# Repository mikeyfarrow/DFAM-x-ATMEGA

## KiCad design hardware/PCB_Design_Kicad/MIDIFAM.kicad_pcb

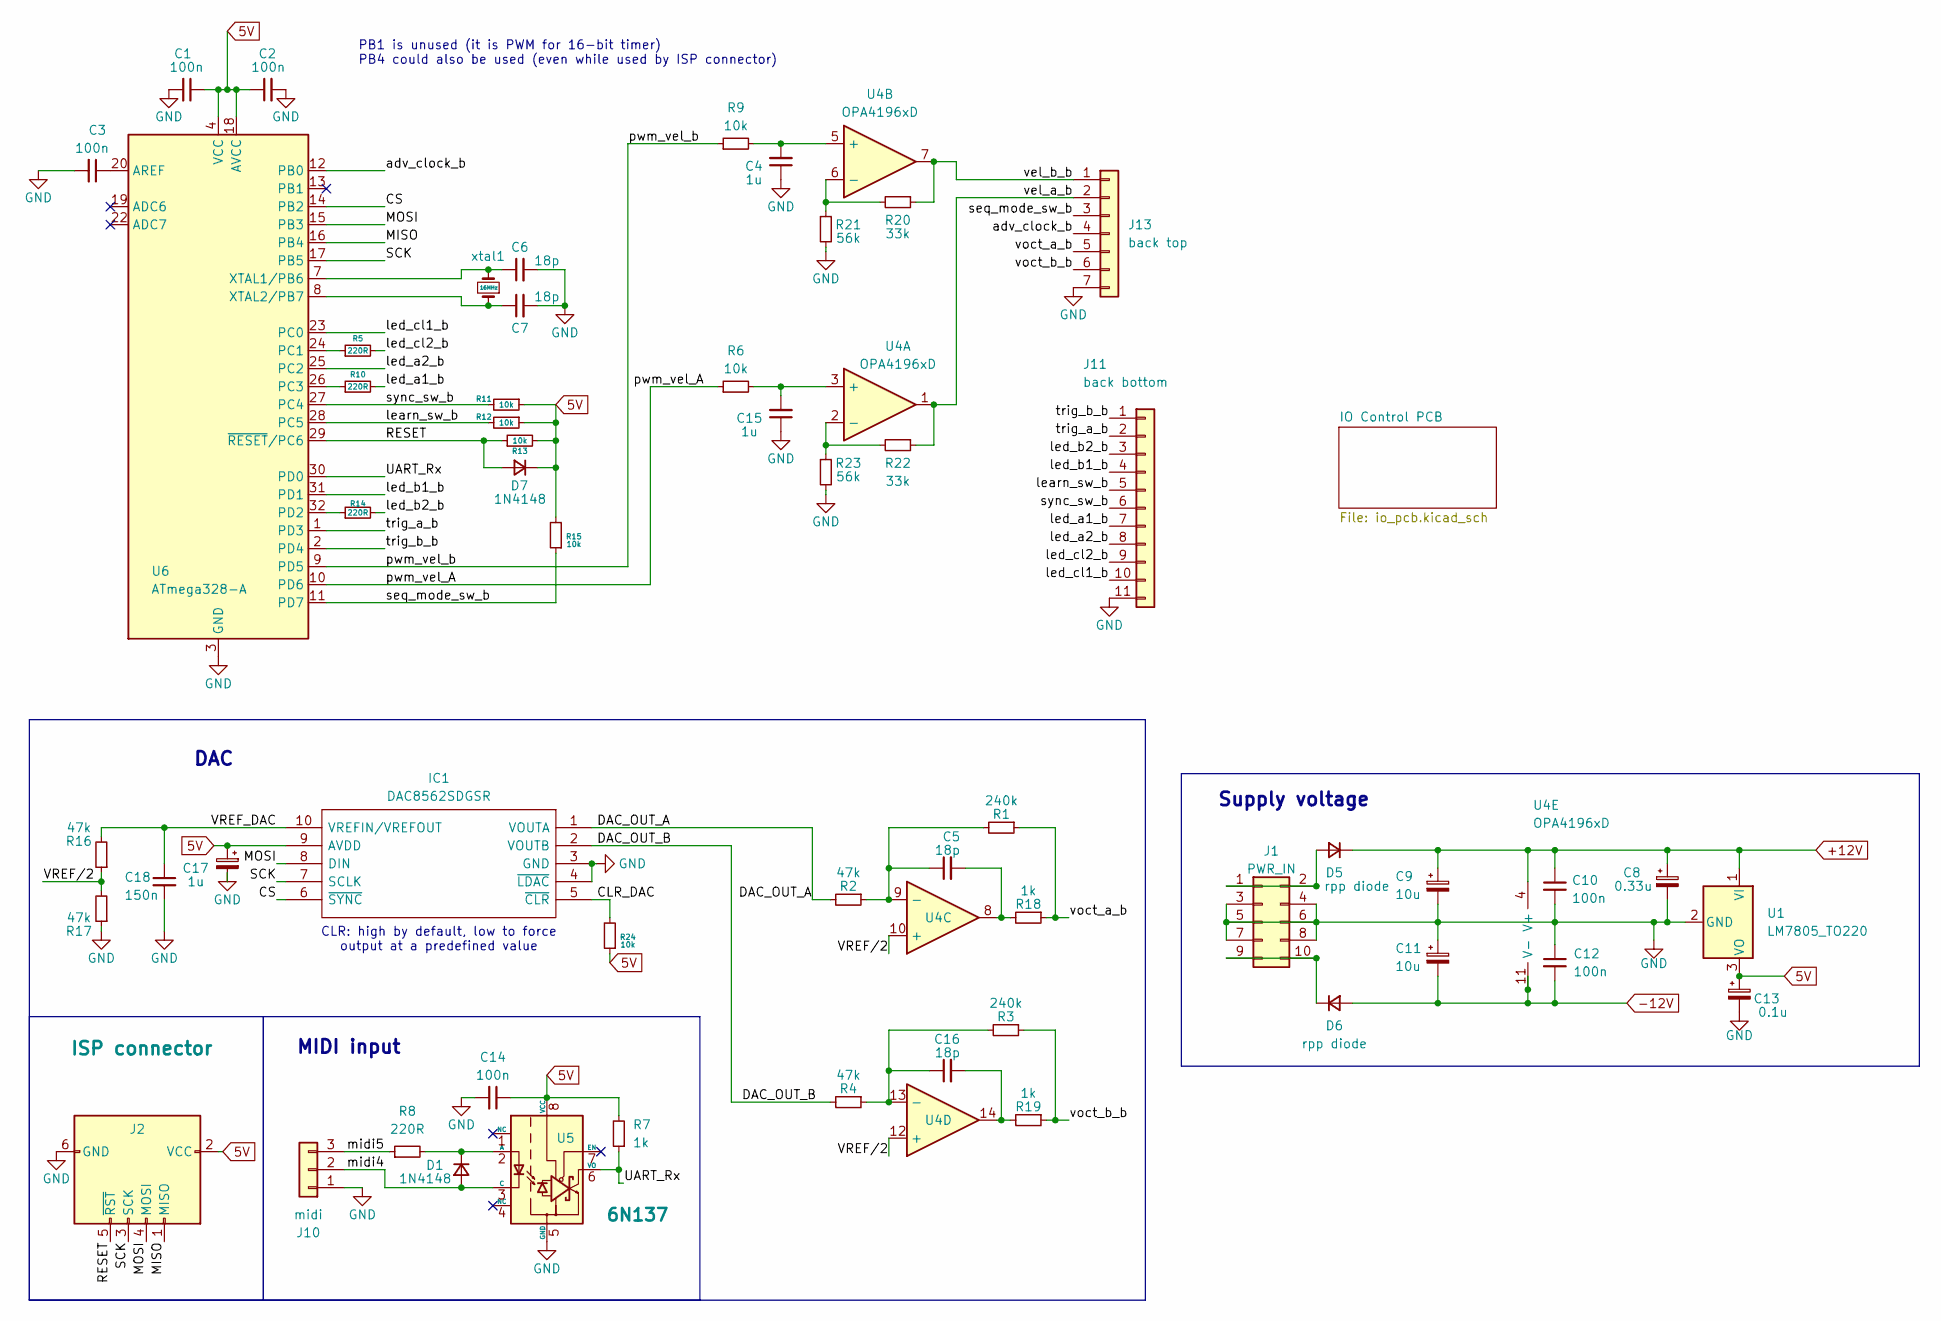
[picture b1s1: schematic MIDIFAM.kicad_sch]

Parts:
C1, C2, C3, C10, C12, C14: 100n; C_0603_1608Metric; LCSC C14663
C4, C15, C17: 1u; C_0603_1608Metric; LCSC C2691405
C5, C6, C7, C16: 18p; C_0603_1608Metric; LCSC C1647
C8: 0.33u; C_0603_1608Metric; LCSC C1623
C9, C11: 10u; CP_Elec_5x5.4; LCSC C263975
C13: 0.1u; C_0603_1608Metric; LCSC C14663
C18: 150n; C_0603_1608Metric; LCSC C464419
D1, D7: 1N4148; D_SOD-323_HandSoldering; LCSC C2128
D5, D6: rpp diode; D_SOD-123F; LCSC C8598
IC1: DAC8562SDGSR; SOP50P490X110-10N; Mouser Part Number 595-DAC8562SDGSR
J1: PWR_IN; PinHeader_2x05_P2.54mm_Vertical
J2: ISP connector; PinHeader_2x03_P2.54mm_Vertical
J10: midi; PinHeader_1x03_P2.54mm_Vertical
J11: back bottom; PinHeader_1x11_P2.54mm_Vertical
J13: back top; PinHeader_1x07_P2.54mm_Vertical
R1, R3: 240k; R_0603_1608Metric_Pad0.98x0.95mm_HandSolder; LCSC C407611
R2, R4, R16, R17: 47k; R_0603_1608Metric_Pad0.98x0.95mm_HandSolder; LCSC C25819
R5, R8, R10, R14: 220R; R_0603_1608Metric_Pad0.98x0.95mm_HandSolder; LCSC C22962
R6, R9, R11, R12, R13, R15, R24: 10k; R_0603_1608Metric_Pad0.98x0.95mm_HandSolder; LCSC C25804
R7, R18, R19: 1k; R_0603_1608Metric_Pad0.98x0.95mm_HandSolder; LCSC C21190
R20, R22: 33k; R_0603_1608Metric_Pad0.98x0.95mm_HandSolder; LCSC C4216
R21, R23: 56k; R_0603_1608Metric_Pad0.98x0.95mm_HandSolder; LCSC C23206
U1: LM7805_TO220; TO-220-3_Horizontal_TabUp
U4: OPA4196xD; TSSOP-14_4.4x5mm_P0.65mm; LCSC C2873620
U5: 6N137; SOP254P1005X465-8N; LCSC C92651
U6: ATmega328-A; TQFP-32_7x7mm_P0.8mm; LCSC C14877
xtal1: 16MHz; XT9M20ANA20M

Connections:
5V: C1.1, C2.1, C13.1, C14.1, C17.1, D7.1 (K), IC1.9 (AVDD), J2.2 (VCC), R7.2, R11.1, R12.1, R13.2, R15.2, R24.1, U1.3 (VO), U5.8 (VCC), U6.4 (VCC), U6.6 (VCC), U6.18 (AVCC)
+12V: C8.1, C9.1, C10.1, D5.1 (K), U1.1 (VI), U4.4 (V+)
-12V: C11.2, C12.2, D6.2 (A), U4.11 (V-)
/CLR_DAC: IC1.5 (~CLR), R24.2
/CS: IC1.6 (~SYNC), U6.14 (PB2)
/DAC_OUT_A: IC1.1 (VOUTA), R2.2
/DAC_OUT_B: IC1.2 (VOUTB), R4.2
/MISO: J2.1 (MISO), U6.16 (PB4)
/MOSI: IC1.8 (DIN), J2.4 (MOSI), U6.15 (PB3)
/RESET: D7.2 (A), J2.5 (~RST), R13.1, U6.29 (~RESET/PC6)
/SCK: IC1.7 (SCLK), J2.3 (SCK), U6.17 (PB5)
/UART_Rx: R7.1, U5.6 (VO), U6.30 (PD0)
/VREF_DAC: C18.1, IC1.10 (VREFIN/VREFOUT), R16.2
/VREF/2: R16.1, R17.2, U4.10 (+), U4.12 (+)
/adv_clock_b: J13.4, U6.12 (PB0)
/learn_sw_b: J11.5, R12.2, U6.28 (PC5)
/led_a1_b: J11.7, R10.2
/led_a2_b: J11.8, U6.25 (PC2)
/led_b1_b: J11.4, U6.31 (PD1)
/led_b2_b: J11.3, R14.2
/led_cl1_b: J11.10, U6.23 (PC0)
/led_cl2_b: J11.9, R5.2
/midi4: D1.2 (A), J10.2, U5.3 (C)
/midi5: J10.3, R8.1
/pwm_vel_A: R6.1, U6.10 (PD6)
/pwm_vel_b: R9.1, U6.9 (PD5)
/seq_mode_sw_b: J13.3, R15.1, U6.11 (PD7)
/sync_sw_b: J11.6, R11.2, U6.27 (PC4)
/trig_a_b: J11.2, U6.1 (PD3)
/trig_b_b: J11.1, U6.2 (PD4)
/vel_a_b: J13.2, R22.1, U4.1
/vel_b_b: J13.1, R20.1, U4.7
/voct_a_b: J13.5, R1.1, R18.1
/voct_b_b: J13.6, R3.1, R19.1
GND: C1.2, C2.2, C3.2, C4.1, C6.2, C7.2, C8.2, C9.2, C10.2, C11.1, C12.1, C13.2, C14.2, C15.1, C17.2, C18.2, IC1.3 (GND), IC1.4 (~LDAC), J1.3, J1.4, J1.5, J1.6, J1.7, J1.8, J2.6 (GND), J10.1, J11.11, J13.7, R17.1, R21.2, R23.2, U1.2 (GND), U5.5 (GND), U6.3 (GND), U6.5 (GND), U6.21 (GND); also elsewhere on the board
unnamed: C5.2, R18.2, U4.8
unnamed: C16.2, R19.2, U4.14
unnamed: D1.1 (K), R8.2, U5.2 (A)
unnamed: D5.2 (A), J1.1, J1.2
unnamed: D6.1 (K), J1.9, J1.10
unnamed: C15.2, R6.2, U4.3 (+)
unnamed: R22.2, R23.1, U4.2 (-)
unnamed: C4.2, R9.2, U4.5 (+)
unnamed: R20.2, R21.1, U4.6 (-)
unnamed: C5.1, R1.2, R2.1, U4.9 (-)
unnamed: C16.1, R3.2, R4.1, U4.13 (-)
unnamed: C3.1, U6.20 (AREF)
unnamed: R5.1, U6.24 (PC1)
unnamed: R10.1, U6.26 (PC3)
unnamed: R14.1, U6.32 (PD2)
unnamed: C6.1, U6.7 (XTAL1/PB6), xtal1.2
unnamed: C7.1, U6.8 (XTAL2/PB7), xtal1.1

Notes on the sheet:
MIDI input
CLR: high by default, low to force output at a predefined value
Supply voltage
PB1 is unused (it is PWM for 16-bit timer) PB4 could also be used (even while used by ISP connector)
DAC

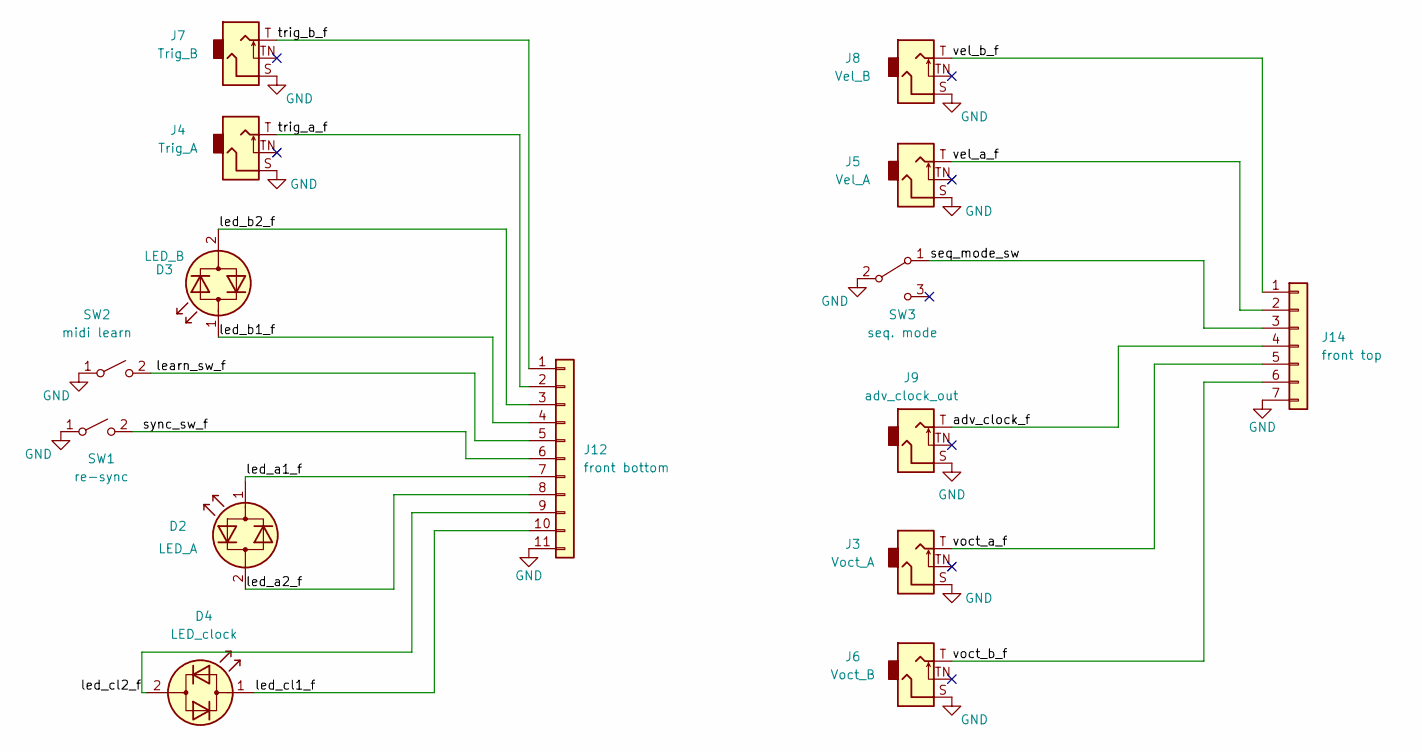
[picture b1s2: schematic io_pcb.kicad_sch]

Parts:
D2: LED_A; LED_D3.0mm_Clear
D3: LED_B; LED_D3.0mm_Clear
D4: LED_clock; LED_D3.0mm_Clear
J3: Voct_A; Thonkiconn
J4: Trig_A; Thonkiconn
J5: Vel_A; Thonkiconn
J6: Voct_B; Thonkiconn
J7: Trig_B; Thonkiconn
J8: Vel_B; Thonkiconn
J9: adv_clock_out; Thonkiconn
J12: front bottom; PinSocket_1x11_P2.54mm_Vertical
J14: front top; PinSocket_1x07_P2.54mm_Vertical
SW1: re-sync; SW_PUSH_6mm_H8mm
SW2: midi learn; SW_PUSH_6mm_H8mm
SW3: seq. mode; submini

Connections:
/IO Control PCB/adv_clock_f: J9.T, J14.4
/IO Control PCB/learn_sw_f: J12.5, SW2.2 (B)
/IO Control PCB/led_a1_f: D2.1 (KA), J12.7
/IO Control PCB/led_a2_f: D2.2 (AK), J12.8
/IO Control PCB/led_b1_f: D3.1 (KA), J12.4
/IO Control PCB/led_b2_f: D3.2 (AK), J12.3
/IO Control PCB/led_cl1_f: D4.1 (KA), J12.10
/IO Control PCB/led_cl2_f: D4.2 (AK), J12.9
/IO Control PCB/seq_mode_sw: J14.3, SW3.1 (A)
/IO Control PCB/sync_sw_f: J12.6, SW1.2 (B)
/IO Control PCB/trig_a_f: J4.T, J12.2
/IO Control PCB/trig_b_f: J7.T, J12.1
/IO Control PCB/vel_a_f: J5.T, J14.2
/IO Control PCB/vel_b_f: J8.T, J14.1
/IO Control PCB/voct_a_f: J3.T, J14.5
/IO Control PCB/voct_b_f: J6.T, J14.6
GND: J3.S, J4.S, J5.S, J6.S, J7.S, J8.S, J9.S, J12.11, J14.7, SW1.1 (A), SW2.1 (A), SW3.2 (B); also elsewhere on the board

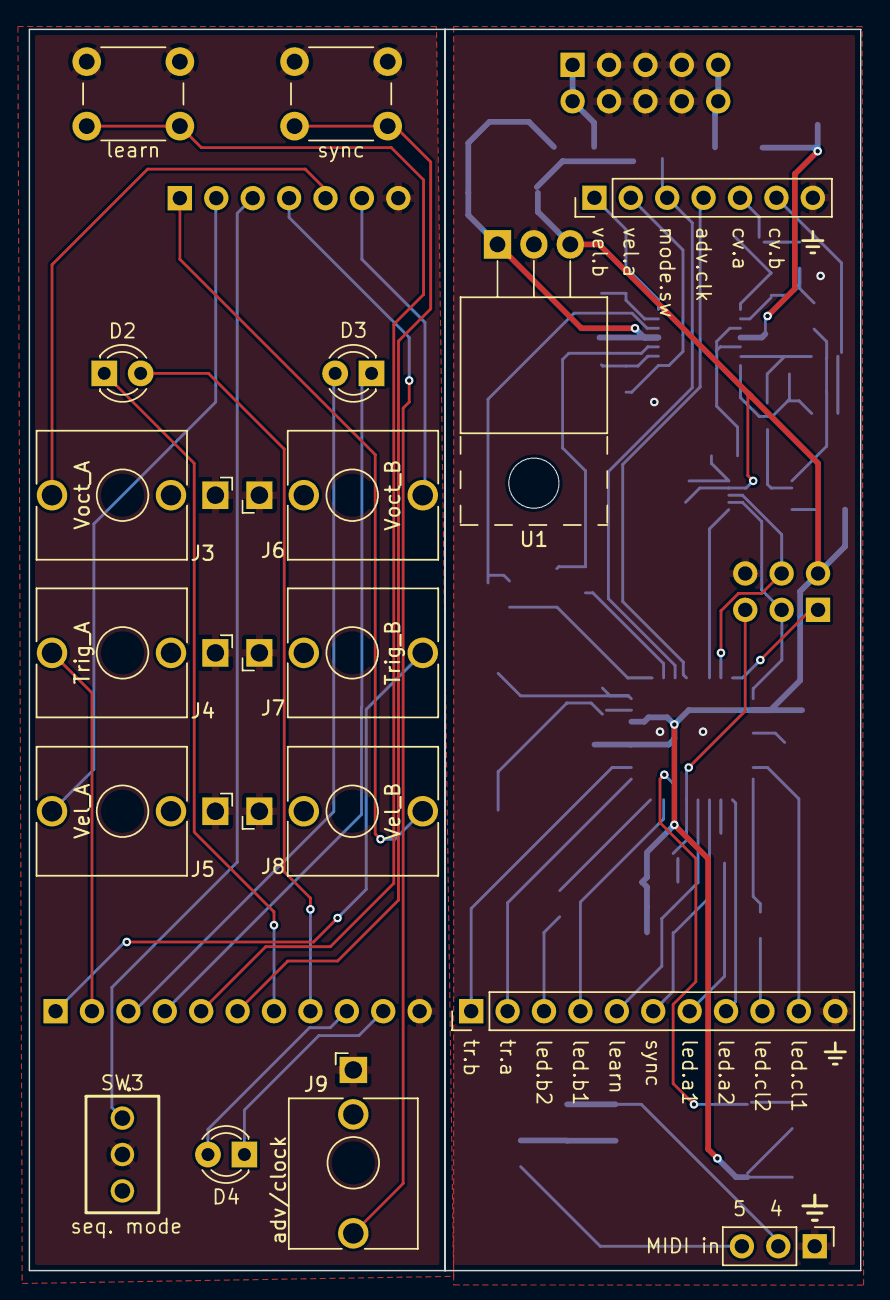
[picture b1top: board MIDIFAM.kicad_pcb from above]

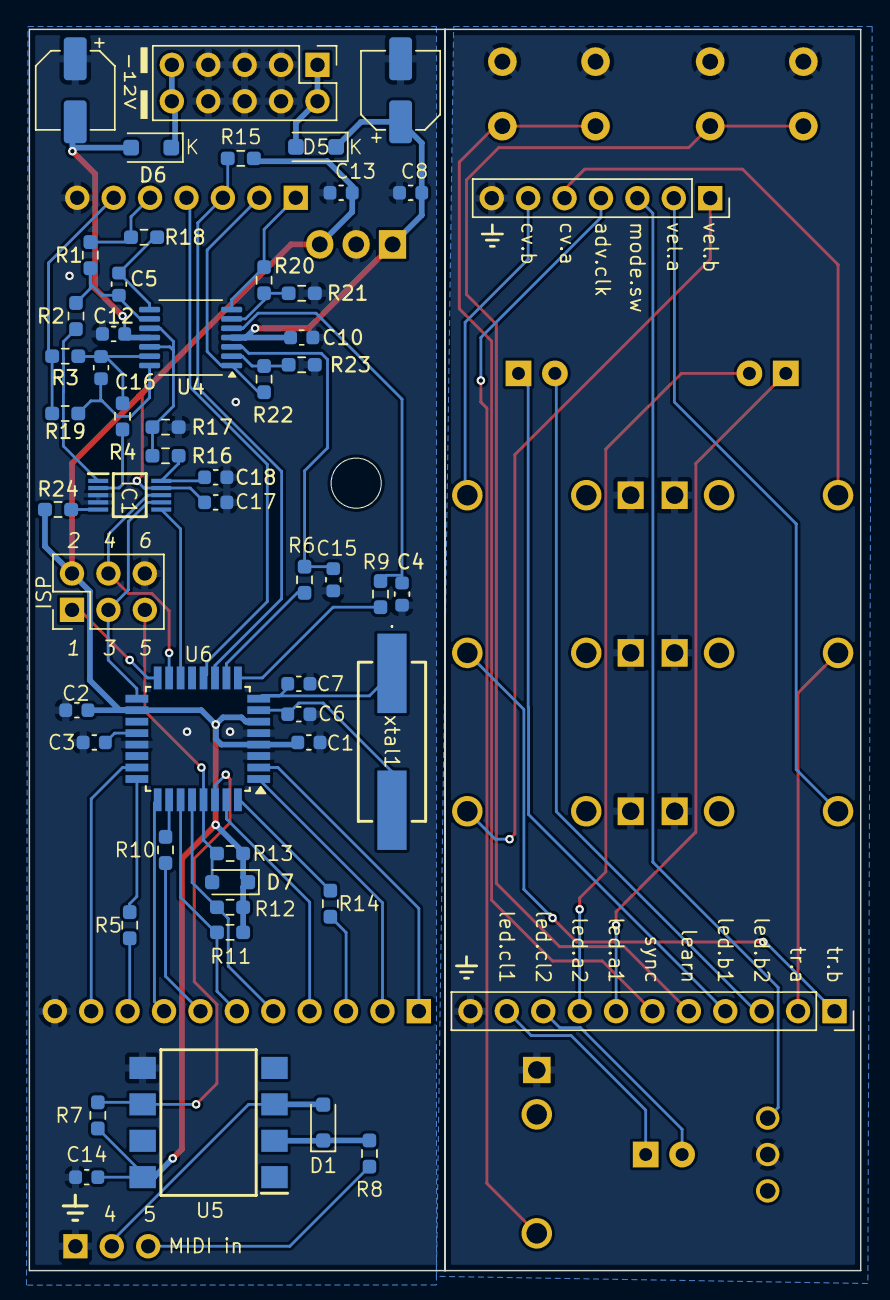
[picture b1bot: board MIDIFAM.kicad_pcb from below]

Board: 2 copper layers, 58.0 x 86.6 mm, 72 parts (55 on the bottom side), 68 nets.

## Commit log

2024-07-03 include copy of arduino MIDI lib
2024-07-03 created microchip studio proj
2024-07-03 replaced transport with empty implementation
2024-07-03 added utilities from previous project
2024-07-04 checkpoint: midi byte loopback working, debug LED banks, and MIDI.h linked
2024-07-04 gitignore build output
2024-07-04 working implementation of MIDI Rx via midi cable
2024-07-04 removing unused code and adding comments
2024-07-04 comments
2024-07-05 organizing code
2024-07-06 initialize SPI for DAC and test 12 bit output
2024-07-06 add trigger timer and eeprom_writer class
2024-07-07 initial implementations of dac V/oct output + run sequencer mode
2024-07-07 initial code for double V/oct & trig outs
2024-07-07 shorter triggers (2 ms)
2024-07-07 implement circular buffer (not used yet)
2024-07-07 implemented circular buffer to store rx midi messages
2024-07-07 moved circ buffer to SerialMidiTransport and modify Transport to use buffer
2024-07-07 rename event handlers
2024-07-07 fixing last two broken commits
2024-07-08 code cleanup, putting away encoder for now because my last encoder is broken
2024-07-08 implement switch input, added led back to bank, debounced switch
2024-07-08 hooking up PWM outputs on timer 0, move trigger interrupts and switch debounce to timer1
2024-07-08 filtered PWM outputs working for velocity
2024-07-08 gitignore
2024-07-08 moved all GPIO macros into a single file, GPIO.h
2024-07-09 reduced note range to 88 notes, added sync button, remapped KCS mode to c major
2024-07-10 trig length and adv/clock duration are tunable via CC messages
2024-07-10 added tunable clock divisions via CC #18
2024-07-10 fix last commit
2024-07-10 code organization
2024-07-10 fixing bug where sequence un-syncs when switching from CCS to KCS
2024-07-11 major refactor - much better now with MidiController class
2024-07-11 better names
2024-07-11 apply velocity and v/oct before trigger
2024-07-11 fix velocity calculation and increase PWM to above audio range (62.5kHz)
2024-07-16 major feature updates: 1. portamento for v/oct, and 2. full MIDI output with Tx ready interrupt
2024-07-19 implement pitch bend + major perf improvements + skeleton of vibrato
2024-07-19 Refactor - create CvOutput to handle sliding and pitchbend separately for each CV channel
2024-07-20 added vibrato with CCs for control
2024-07-20 fixed phase of triangle wave vibrato
2024-07-21 moved dac output to CvOutput class
2024-07-22 fixed midi note range bug. added initial sketch for polyphonic / note priority ideas
2024-07-22 better cc handling
2024-07-22 basic midi channels are now variables
2024-07-22 remove unused function
2024-07-23 added midi channel select mode; added asc/desc portamento CCs; fixed DAC data overflow bugs
2024-07-23 vibrato and portamento concurrently; initial BPM detection math
2024-07-23 templated CircularBuffer. Accurate BPM calculation.
2024-07-23 better tempo sync'd delay - can switch on and off. todo: apply vibrato delay at note_on, don't update with every cc
2024-07-24 added "latest" note priority implementation; TODO: MIDI mode messages and a UI for latest/highest/lowest
2024-07-29 added retrigger behavior; initial implementation of MIDI poly mode
2024-07-29 rest of changes
2024-07-30 trig mode and gate mode for trigger outputs; better poly mode
2024-07-30 added more CCs
2024-08-02 initial digital calibration logic; save and load to/from EEPROM
2024-08-02 LFO mode (halfwave, rectified, bipolar) for vibrato
2024-08-03 push button events with keyboard learn mode; better cc ranges for most params
2024-08-03 adding kicad schematic and PCB drafts
2024-08-09 SMD pcb, routable and with vias
2024-08-09 routed SMD
2024-08-09 better routing
2024-08-10 fix footprints and jack position
2024-08-10 good routing and ground planes
2024-08-11 ready for schematic review
2024-08-12 op amps for velocity!
2024-08-12 updating code to work with new LED setup
2024-08-13 adding to BOM
2024-08-13 more bom
2024-08-13 panel
2024-08-22 pcb versions sent to jlcpcb
2024-09-09 initial functionality for SMD assembly with new DAC (DAC8562)
2024-09-11 dac8562 calibration procedure
2024-09-11 removing dac interpolation (for now)
2024-09-12 directory structury organization
2024-09-15 bootloader w midi sysex
2024-09-16 reorganized for new Makefile build system
2024-09-16 better makefile
2024-09-16 remove unnecessary macros from makefile
2024-09-18 better MIDI channel selection
2024-09-18 better make
2024-09-23 trigger C led in KCS mode
